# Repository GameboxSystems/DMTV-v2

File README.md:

# DMTV v2

DMTV or "Dot Matrix Television" is an embedded solution to pair with a an original GameBoy console to provide 800x600 60Hz VGA out graphics, NES controller input, custom color palettes, and toggleable scanlines.

Unlike the original DMTV, this version no longer requires an atmega32u4 for controller handling. This feature is now baked directly into the source code using a simple shift register! This allows for a simplified board and lower BOM cost than before. Also includes all new color palettes.

To access scanlines and alternate color palettes, simply press Start + Select + A/B. The toggle is executed on the falling edge of the button press.

## Changes From v1

* No atmega32u4 for controller handling. This is now done by the FPGA via the nes_controller.v
* Addition of mosfet/diode arrays to simulate button presses for the Game Boy.
* Nes Port now built in!
* Mono audio included in ribbon cable. One wire required for pro sound mod.
* Greatly reduced BOM cost
* Color palettes don't hurt the eyes as much

## Getting Started

### Prerequisites

* Assembled DMTV v2 board (keep spi flash off board until after flashing)
* Windows/Linux computer (linux HIGHLY recommended)
* [APIO Icestorm](https://apiodoc.readthedocs.io/en/stable/) (iceCube2 will **NOT** synthesize source code correctly as it is not as optimized as APIO)
	* Either compile from source using APIO Icestorm or use provided precompiled binary
	* You can find install instructions on multiple platforms [here](https://apiodoc.readthedocs.io/en/stable/source/installation.html)
* Pomona SOIC-Clip Model 5252/buspirate v3.6 combo
	* This combo is for bypassing the expensive Lattice Diamond programmer cable
	* Pomona clip: https://www.digikey.com/product-detail/en/pomona-electronics/5252/501-2059-ND/745103
	* Buspirate v3.6: https://www.sparkfun.com/products/12942
* [flashrom](https://www.flashrom.org/Flashrom) 
* Not in the BOM, but a right angle NES port is required for controller support. You can find them [here](https://www.zedlabz.com/products/zedlabz-7-pin-90-degree-female-controller-connector-port-for-nintendo-nes-console-2-pack-black)

### Flashing FPGA SPI Flash Memory

Once a binary is obtained either through synthesis of source or using the precompiled binary, connect the buspirate to the SOIC clip as shown below.

If using a binary output from APIO, you must resize the binary. Flashrom will not flash the spi memory until it is sized properly. Linux users, use the truncate command and windows users use your favorite hex editor to resize the binary.

For instructions on how to use buspirate with flashrom, use the official buspirate page on the flashrom website found here: https://flashrom.org/Bus_Pirate

After successful flash, solder to DMTV PCB.

### Notes on the HDL Code / Hardware

* Color palettes can be swapped for different color palettes if desired. The color code is RGB565 so any color space higher than that will need to be translated down. RGB888 can be added via hardware if desired as well, it will however reduce the amount of logic elements.
* If a different screen resolution is desired, swap out the current 40MHz oscillator for an oscialltor that matches timings consistant with that frequency. The code will need to be changed to reflect the profile as well. Use VGA profiles found here: http://tinyvga.com/vga-timing
* Resistor values go from greatest to smallest and are assigned such that the least significant assigned output pin for RGB goes to the highest ohm resistor downwards
	* i.e. R0 -> 8kohm, G -> 16kohm, B -> 8kohm, etc.

## Currently Known Issues

* Non currently found, please submit a pull request if you find one

## ToDo

* Add option to flash SPI flash via header instead
	* This was a challenge as there needs to be a way to sever the 3.3v power rail. If the SPI flash and the FPGA both have power then the SPI flash is not detected. The only work around known is to flash the SPI flash off the board and solder it on after flashing.
* SNES controller support

## Built With

* [APIO Icestorm](https://github.com/FPGAwars/apio)
* flashrom
* Eagle
* Sublime Text

## Versions

v1.0 - Initial release

## Contributing

Please feel free to issue a PR or edit code freely. Would love to have people contribute ideas!

## Authors

* **Postman** - *Head of engineering at Gamebox Systems*

## License

This project is licensed under the GPL-3.0 license, see attached license for info.

## Acknowledgments

* **ahhuhtal** - *DMTV v2 is based off of their gbvga project. Ahhuhtal, thank you for your wonderful description of how the first active pixel is after the falling edge of HSync. I was stuck on that for a long time.* - [ahhuhtal](https://github.com/ahhuhtal)

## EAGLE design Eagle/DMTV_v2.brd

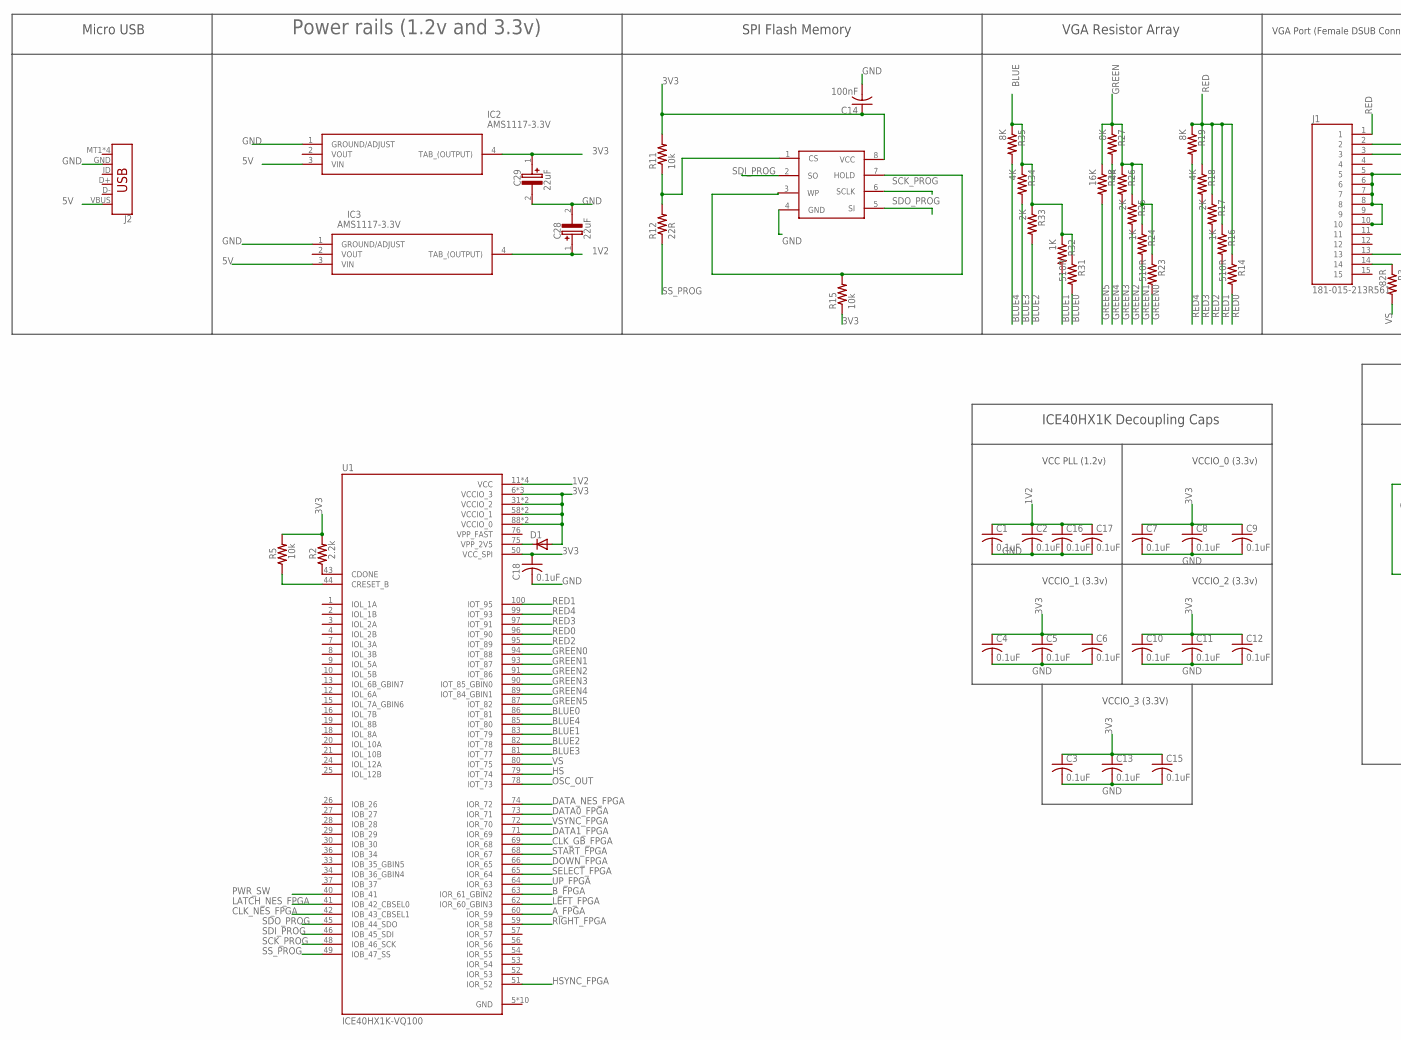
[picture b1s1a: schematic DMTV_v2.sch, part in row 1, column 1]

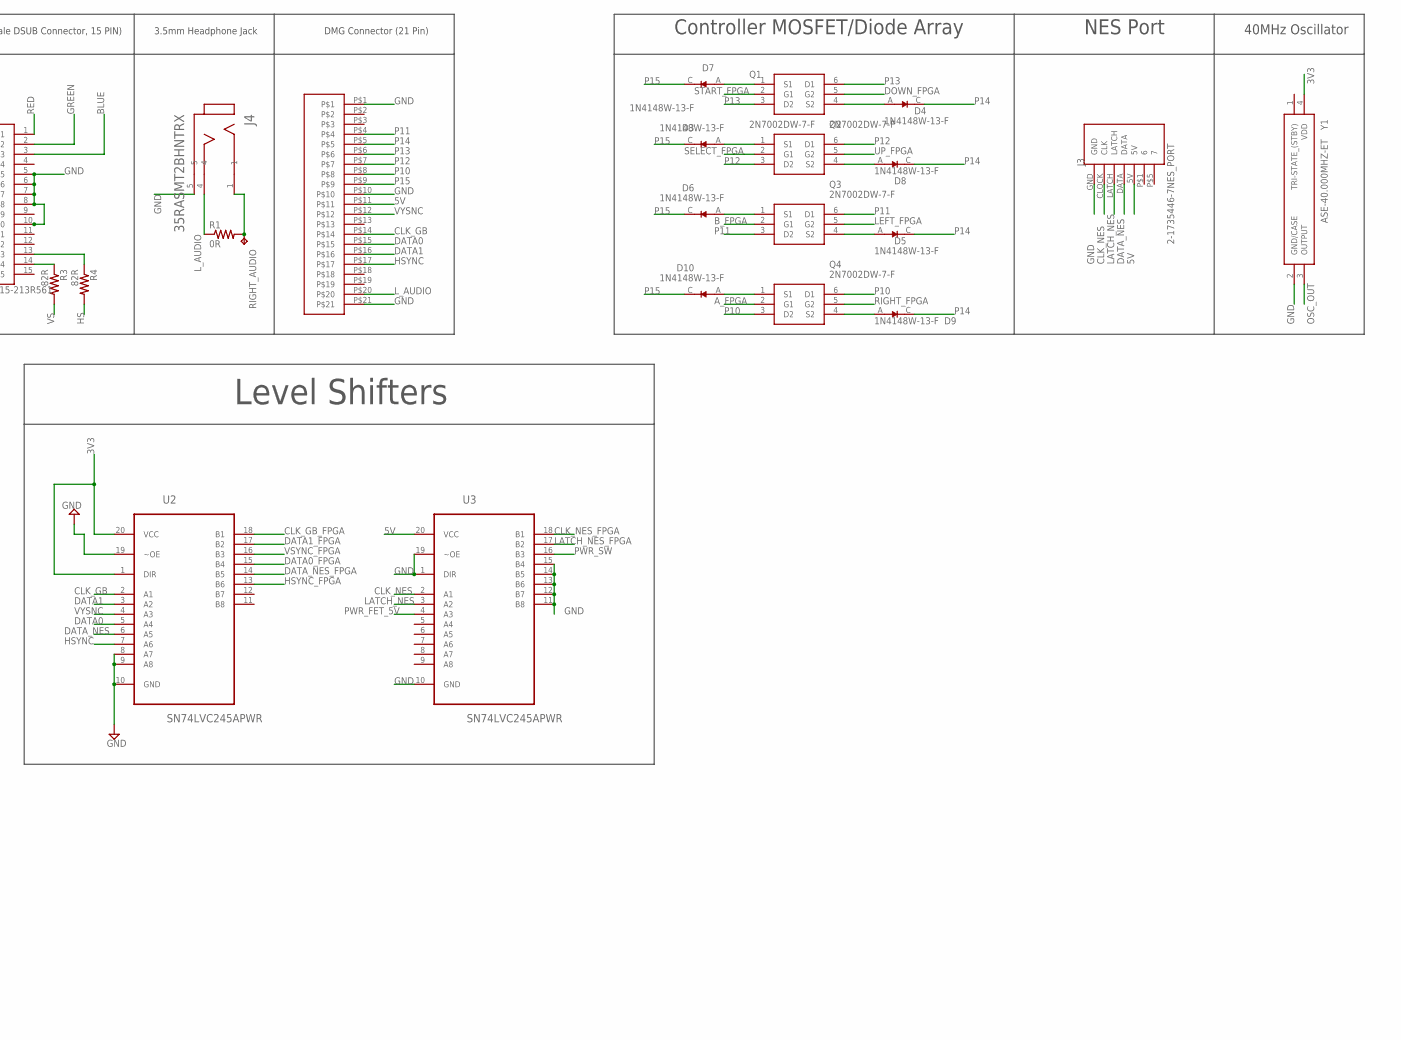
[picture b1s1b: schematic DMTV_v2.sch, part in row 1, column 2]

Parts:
C1, C2, C3, C4, C5, C6, C7, C8, C9, C10, C11, C12, C13, C15, C16, C17, C18: 0.1uF; C0603
C14: 100nF; C0603
C28, C29: 22uF; CAPPM3216X180N
D1: D-SOD123; SOD123
D3, D4, D5, D6, D7, D8, D9, D10: 1N4148W-13-F; SOD3715X135N
IC2, IC3: AMS1117-3.3V; SOT229P700X180-4N
J1: 181-015-213R561; NORCOMP_181-015-213R561
J2: USB_MICRO-B_SMT; USB-MICROB
J3: 2-1735446-7NES_PORT; NES_CONTROLLER_SOLDER_JACK
J4: 35RASMT2BHNTRX; SWITCHCRAFT_35RASMT2BHNTRX
Q1, Q2, Q3, Q4: 2N7002DW-7-F; SOT65P210X100-6N
R1: 0R; R0603
R2: 2.2k; R0603
R3, R4: 82R; R0603
R5, R11, R15: 10k; R0603
R12: 22R; R0603
R14, R23, R31: 510R; R0603
R16, R24, R32: 1K; R0603
R17, R25, R33: 2K; R0603
R18, R26, R34: 4K; R0603
R19, R27, R35: 8K; R0603
R28: 16K; R0603
RIGHT_AUDIO: TPB2,54; B2,54
U1: ICE40HX1K-VQ100; QFP50P1600X1600X120-100N
U2, U3: SN74LVC245APWR; SOP65P640X120-20N
U$5: MX25L1006EMI-10G; SOIC-8
U$6: 52808-21700520452145; 0520452145
Y1: ASE-40.000MHZ-ET; ASE40000MHZET

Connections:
1V2: C1.1, C2.1, C16.1, C17.1, C28.1 (+), IC3.4 (TAB_(OUTPUT)), U1.11 (VCC), U1.35 (VCC), U1.61 (VCC), U1.77 (VCC)
3V3: C3.1, C4.1, C5.1, C6.1, C7.1, C8.1, C9.1, C10.1, C11.1, C12.1, C13.1, C14.1, C15.1, C18.1, C29.1 (+), D1.2 (A), IC2.4 (TAB_(OUTPUT)), R2.2, R5.2, R11.2, R15.1, U1.6 (VCCIO_3), U1.14 (VCCIO_3), U1.22 (VCCIO_3), U1.31 (VCCIO_2), U1.38 (VCCIO_2), U1.50 (VCC_SPI), U1.58 (VCCIO_1), U1.67 (VCCIO_1), U1.88 (VCCIO_0), U1.92 (VCCIO_0), U2.1 (DIR), U2.20 (VCC), U$5.8 (VCC), Y1.4 (VDD)
5V: IC2.3 (VIN), IC3.3 (VIN), J2.VBUS, J3.5V, U3.20 (VCC), U$6.P$11
A_FPGA: Q4.2 (G1), U1.60 (IOR_59)
BLUE: J1.3, R31.1, R32.1, R33.1, R34.1, R35.1
BLUE0: R31.2, U1.86 (IOT_81)
BLUE1: R32.2, U1.83 (IOT_79)
BLUE2: R33.2, U1.82 (IOT_78)
BLUE3: R34.2, U1.81 (IOT_77)
BLUE4: R35.2, U1.85 (IOT_80)
B_FPGA: Q3.2 (G1), U1.63 (IOR_61_GBIN2)
CLK_GB: U2.2 (A1), U$6.P$14
CLK_GB_FPGA: U1.69 (IOR_68), U2.18 (B1)
CLK_NES: J3.CLOCK (CLK), U3.2 (A1)
CLK_NES_FPGA: U1.42 (IOB_43_CBSEL1), U3.18 (B1)
DATA0: U2.5 (A4), U$6.P$15
DATA0_FPGA: U1.73 (IOR_71), U2.15 (B4)
DATA1: U2.3 (A2), U$6.P$16
DATA1_FPGA: U1.71 (IOR_69), U2.17 (B2)
DATA_NES: J3.DATA, U2.6 (A5)
DATA_NES_FPGA: U1.74 (IOR_72), U2.14 (B5)
DOWN_FPGA: Q1.5 (G2), U1.66 (IOR_65)
GND: C1.2, C2.2, C3.2, C4.2, C5.2, C6.2, C7.2, C8.2, C9.2, C10.2, C11.2, C12.2, C13.2, C14.2, C15.2, C16.2, C17.2, C18.2, C28.2 (-), C29.2 (-), IC2.1 (GROUND/ADJUST), IC3.1 (GROUND/ADJUST), J1.5, J1.6, J1.7, J1.8, J1.10, J2.GND, J3.GND, J4.5, U1.5 (GND), U1.17 (GND), U1.23 (GND), U1.32 (GND), U1.39 (GND), U1.47 (GND), U1.55 (GND), U1.70 (GND), U1.84 (GND), U1.98 (GND), U2.8 (A7), U2.9 (A8), U2.10 (GND), U2.19 (~OE), U3.1 (DIR), U3.10 (GND), U3.11 (B8), U3.12 (B7), U3.13 (B6), U3.14 (B5), U3.15 (B4), U3.19 (~OE), U$5.4 (GND), U$6.P$1, U$6.P$10, U$6.P$21, Y1.2 (GND/CASE)
GREEN: J1.2, R23.1, R24.1, R25.1, R26.1, R27.1, R28.1
GREEN0: R23.2, U1.94 (IOT_88)
GREEN1: R24.2, U1.93 (IOT_87)
GREEN2: R25.2, U1.91 (IOT_86)
GREEN3: R26.2, U1.90 (IOT_85_GBIN0)
GREEN4: R27.2, U1.89 (IOT_84_GBIN1)
GREEN5: R28.2, U1.87 (IOT_82)
HS: R4.2, U1.79 (IOT_74)
HSYNC: U2.7 (A6), U$6.P$17
HSYNC_FPGA: U1.51 (IOR_52), U2.13 (B6)
LATCH_NES: J3.LATCH, U3.3 (A2)
LATCH_NES_FPGA: U1.41 (IOB_42_CBSEL0), U3.17 (B2)
LEFT_FPGA: Q3.5 (G2), U1.62 (IOR_60_GBIN3)
L_AUDIO: J4.4, R1.1, U$6.P$20
unnamed: D1.1 (C), U1.75 (VPP_2V5)
unnamed: D7.A, Q1.1 (S1)
unnamed: J1.14, R3.1
unnamed: J1.13, R4.1
unnamed: J4.1, R1.2, RIGHT_AUDIO.TP
unnamed: R2.1, U1.43 (CDONE)
unnamed: R5.1, U1.44 (CRESET_B)
unnamed: R11.1, R12.2, U$5.1 (CS)
unnamed: D4.A, Q1.4 (S2)
unnamed: D3.A, Q2.1 (S1)
unnamed: D8.A, Q2.4 (S2)
unnamed: R15.2, U$5.3 (WP), U$5.7 (HOLD)
unnamed: D5.A, Q3.4 (S2)
unnamed: D9.A, Q4.4 (S2)
unnamed: D10.A, Q4.1 (S1)
unnamed: D6.A, Q3.1 (S1)
OSC_OUT: U1.78 (IOT_73), Y1.3 (OUTPUT)
P10: Q4.3 (D2), Q4.6 (D1), U$6.P$8
P11: Q3.3 (D2), Q3.6 (D1), U$6.P$4
P12: Q2.3 (D2), Q2.6 (D1), U$6.P$7
P13: Q1.3 (D2), Q1.6 (D1), U$6.P$6
P14: D4.C (K), D5.C (K), D8.C (K), D9.C (K), U$6.P$5
P15: D3.C (K), D6.C (K), D7.C (K), D10.C (K), U$6.P$9
PWR_FET_5V: U3.4 (A3)
PWR_SW: U1.40 (IOB_41), U3.16 (B3)
RED: J1.1, R14.1, R16.1, R17.1, R18.1, R19.1
RED0: R14.2, U1.96 (IOT_90)
RED1: R16.2, U1.100 (IOT_95)
RED2: R17.2, U1.95 (IOT_89)
RED3: R18.2, U1.97 (IOT_91)
RED4: R19.2, U1.99 (IOT_93)
RIGHT_FPGA: Q4.5 (G2), U1.59 (IOR_58)
SCK_PROG: U1.48 (IOB_46_SCK), U$5.6 (SCLK)
SDI_PROG: U1.46 (IOB_45_SDI), U$5.2 (SO)
SDO_PROG: U1.45 (IOB_44_SDO), U$5.5 (SI)
SELECT_FPGA: Q2.2 (G1), U1.65 (IOR_64)
SS_PROG: R12.1, U1.49 (IOB_47_SS)
START_FPGA: Q1.2 (G1), U1.68 (IOR_67)
UP_FPGA: Q2.5 (G2), U1.64 (IOR_63)
VPP_FAST: U1.76 (VPP_FAST)
VS: R3.2, U1.80 (IOT_75)
VSYNC_FPGA: U1.72 (IOR_70), U2.16 (B3)
VYSNC: U2.4 (A3), U$6.P$12

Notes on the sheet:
VCC PLL (1.2v)
VCCIO_0 (3.3v)
VCCIO_1 (3.3v)
VCCIO_2 (3.3v)
VCCIO_3 (3.3V)
ICE40HX1K Decoupling Caps
VGA Resistor Array
VGA Port (Female DSUB Connector, 15 PIN)
SPI Flash Memory
Power rails (1.2v and 3.3v)
Level Shifters
3.5mm Headphone Jack
DMG Connector (21 Pin)
Micro USB
Controller MOSFET/Diode Array
NES Port
40MHz Oscillator

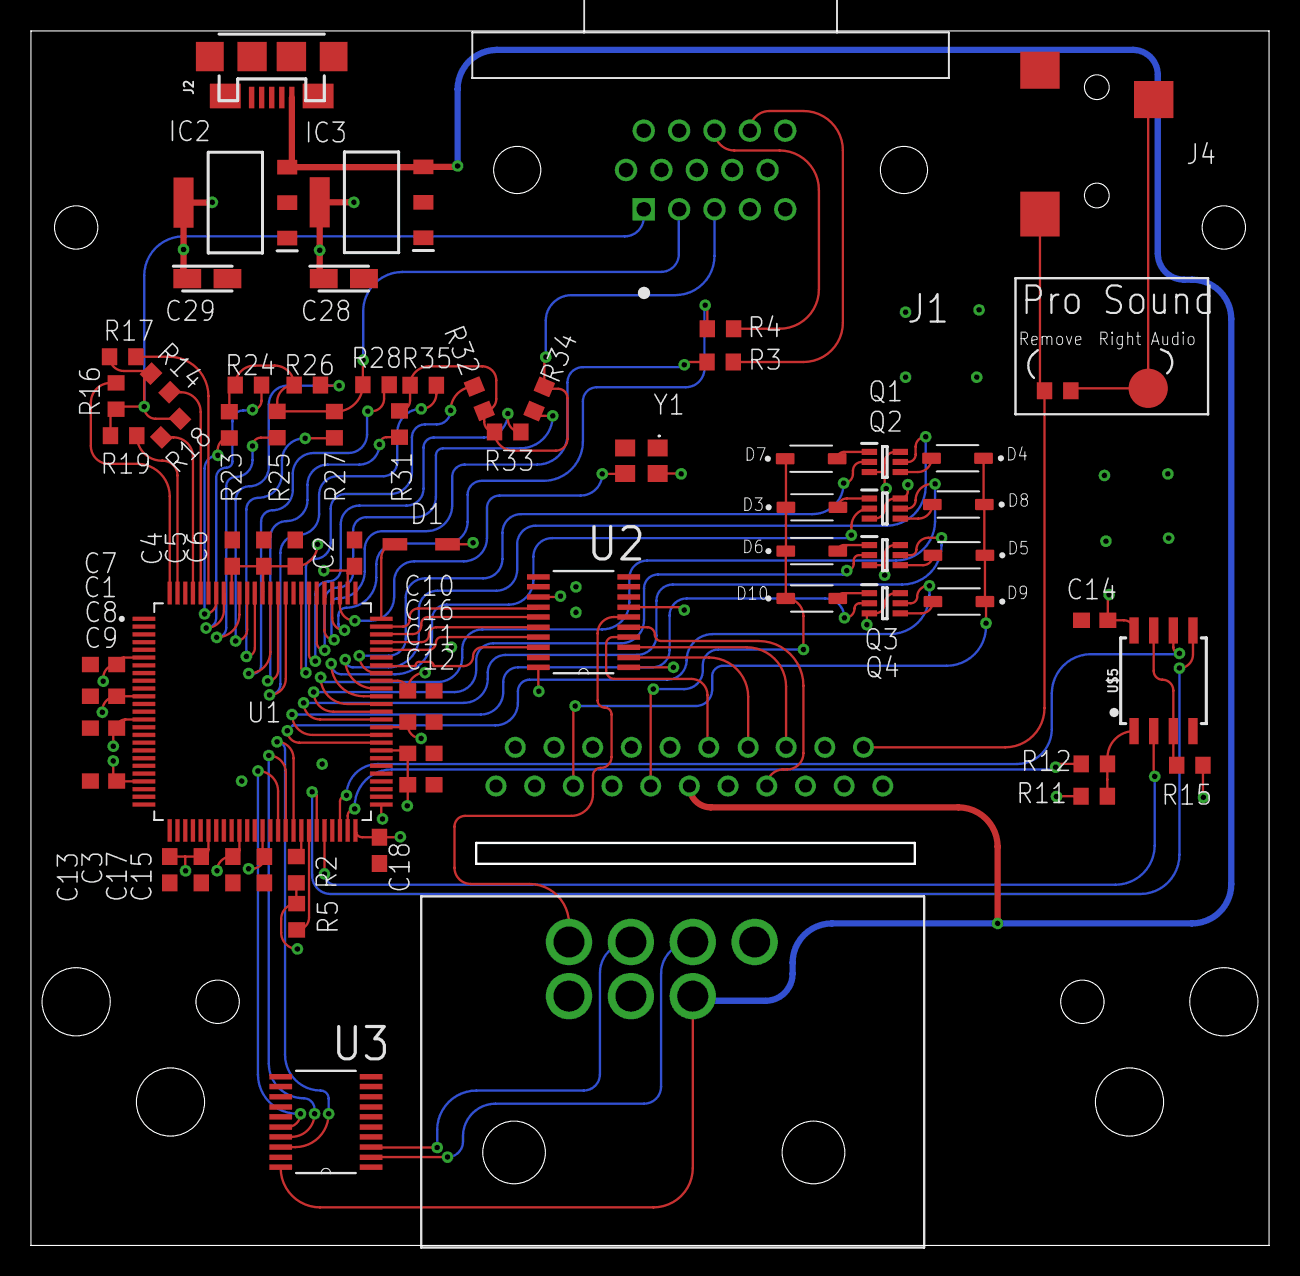
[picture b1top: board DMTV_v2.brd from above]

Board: 4 copper layers, 79.9 x 78.3 mm, 71 parts (1 on the bottom side), 78 nets.

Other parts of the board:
U$1: DMTVPLS

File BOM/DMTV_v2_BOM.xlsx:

Qty | Value | Package | Parts
17 | 0.1uF | C0603 | C1, C2, C3, C4, C5, C6, C7, C8, C9, C10, C11, C12, C13, C15, C16, C17, C18
1 | 100nF | C0603 | C14
2 | 22uF | CAPPM3216X180N | C28, C29
1 |  | SOD123 | D1
8 | 1N4148W-13-F | SOD3715X135N | D3, D4, D5, D6, D7, D8, D9, D10
1 | AMS1117-3.3 | SOT229P700X180-4N | IC2
1 | AMS1117-1.2 | SOT229P700X180-4N | IC3
1 | 181-015-213R561 | NORCOMP_181-015-213R561 | J1
1 |  | USB-MICROB | J2
1 | 2-1735446-7NES_PORT | NES_CONTROLLER_SOLDER_JACK | J3
1 | 35RASMT2BHNTRX | SWITCHCRAFT_35RASMT2BHNTRX | J4
4 | 2N7002DW-7-F | SOT65P210X100-6N | Q1, Q2, Q3, Q4
1 | 0R | R0603 | R1
1 | 22R | R0603 | R12
3 | 510R | R0603 | R14, R23, R31
3 | 1K | R0603 | R16, R24, R32
3 | 2K | R0603 | R17, R25, R33
3 | 4K | R0603 | R18, R26, R34
3 | 8K | R0603 | R19, R27, R35
1 | 2.2k | R0603 | R2
1 | 16K | R0603 | R28
2 | 82R | R0603 | R3, R4
3 | 10k | R0603 | R5, R11, R15
1 | MX25L1006EMI-10G | SOIC-8 | U$5
1 | 52808-21700520452145 | 520452145 | U$6
1 | ICE40HX1K-VQ100 | QFP50P1600X1600X120-100N | U1
2 | SN74LVC245APWR | SOP65P640X120-20N | U2, U3
1 | SI2301BDS | SOT95P240X111-3N | U5
1 | ASE-40.000MHZ-ET | SMD-3225_4P | Y1

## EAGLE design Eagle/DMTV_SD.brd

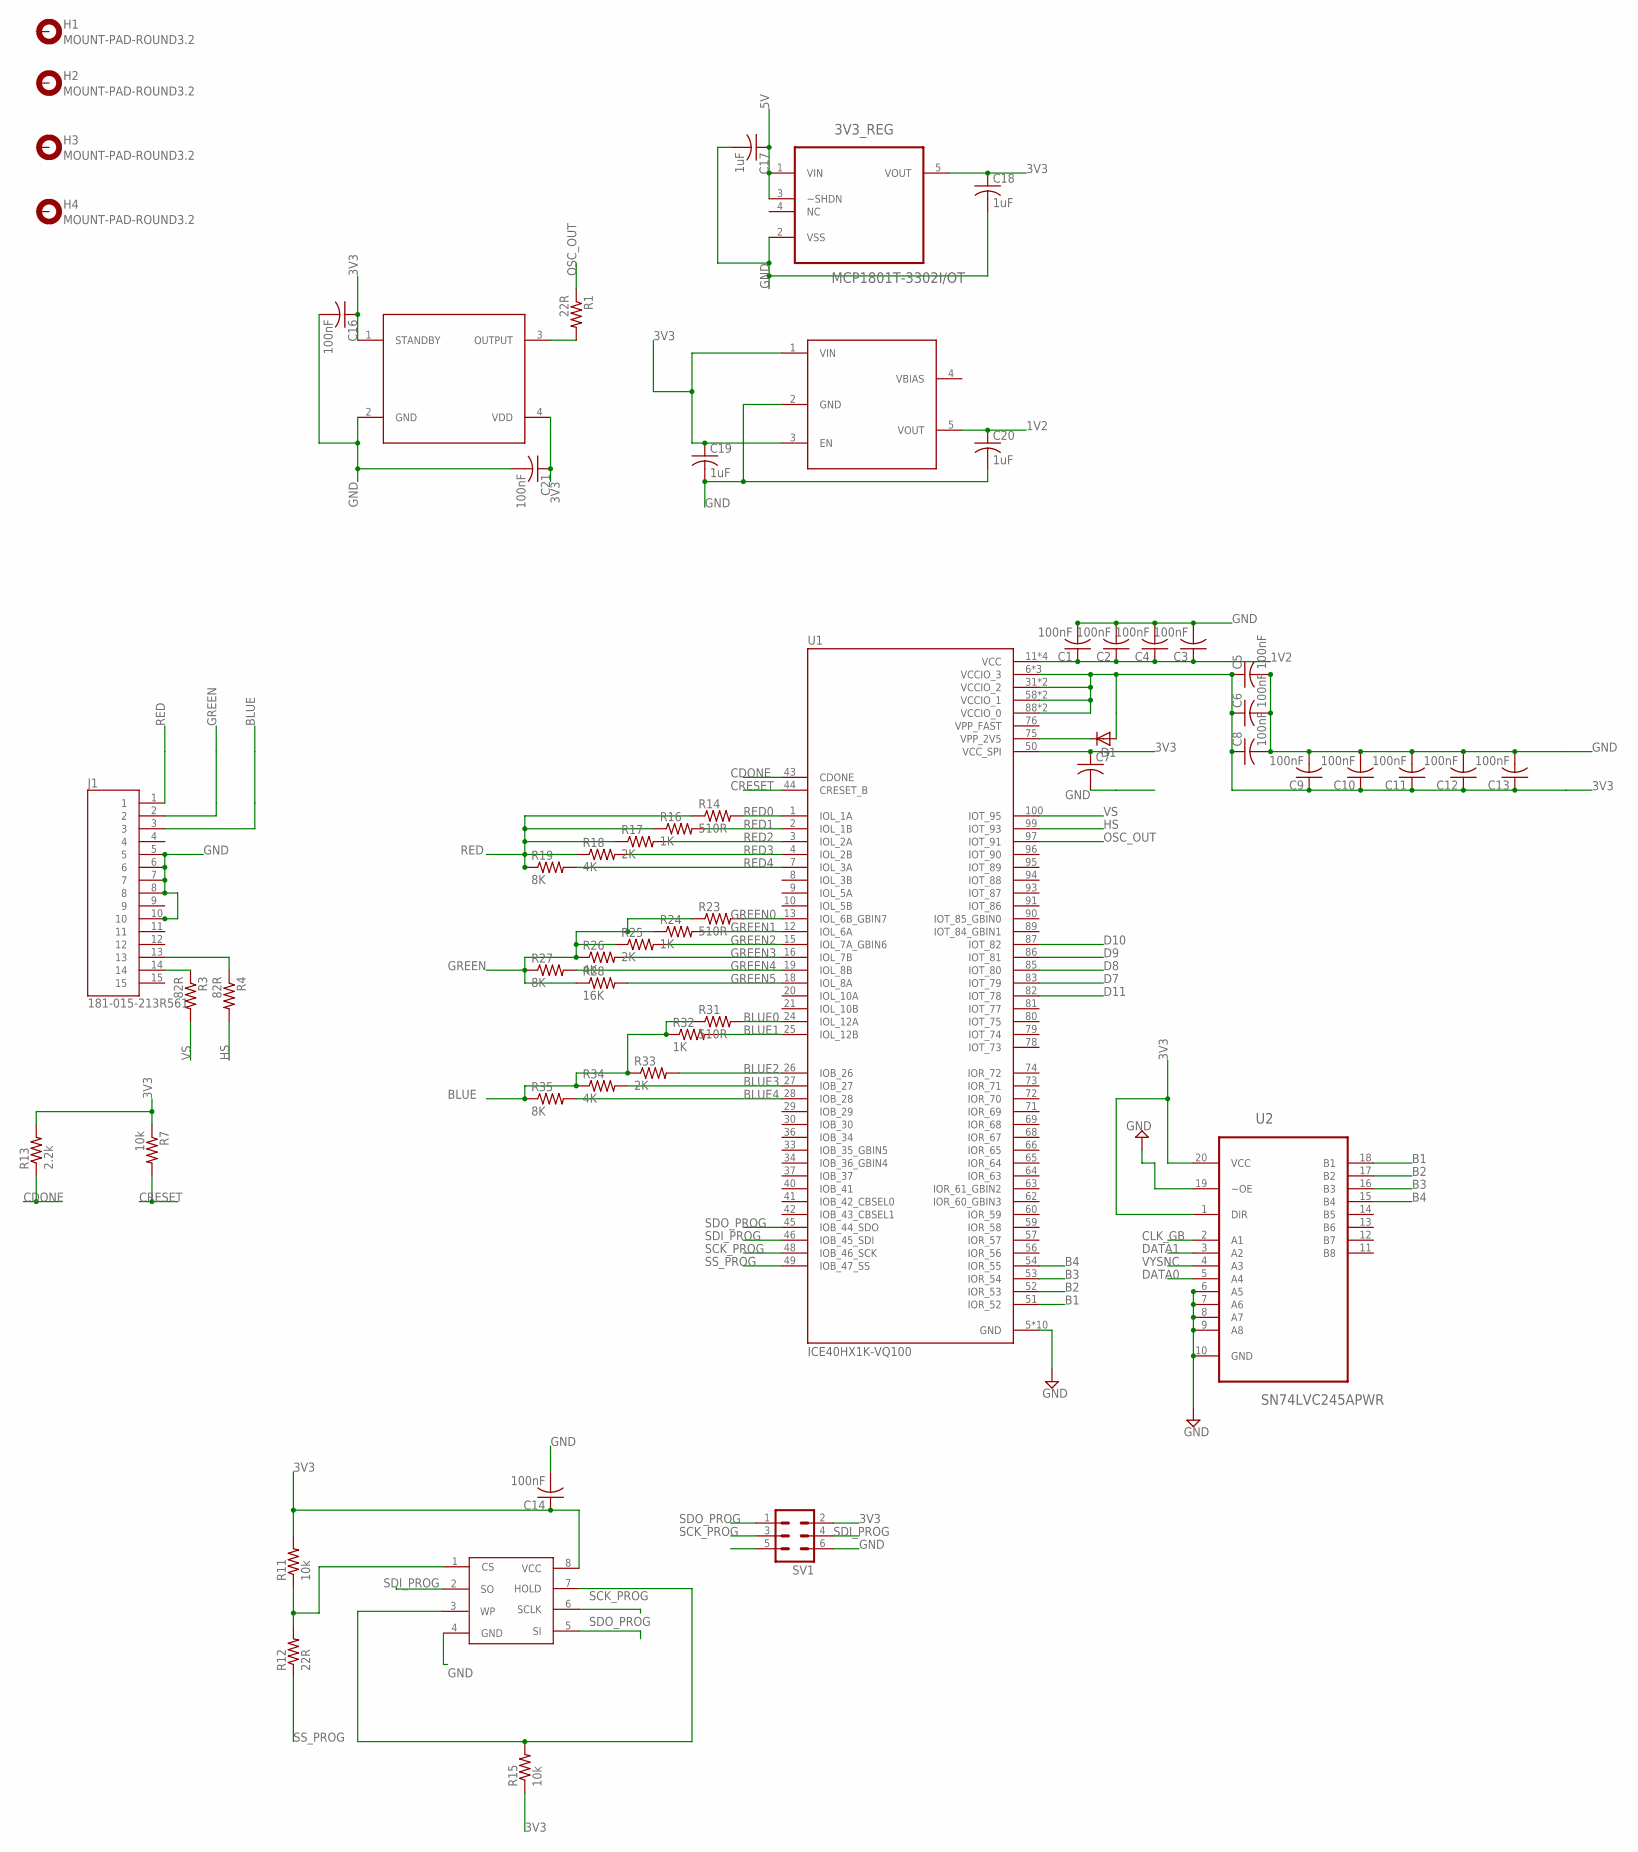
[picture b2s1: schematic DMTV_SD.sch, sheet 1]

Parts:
3V3_REG: MCP1801T-3302I/OT; SOT95P270X145-5N
C1, C2, C3, C4, C5, C6, C8, C9, C10, C11, C12, C13, C14, C16, C21: 100nF; C0603
C7: C-USC0603; C0603
C17, C18, C19, C20: 1uF; C0805
D1: D-SOD123; SOD123
H1, H2, H3, H4: MOUNT-PAD-ROUND3.2; 3,2-PAD
J1: 181-015-213R561; NORCOMP_181-015-213R561
R1, R12: 22R; R0603
R3, R4: 82R; R0603
R7, R11, R15: 10k; R0603
R13: 2.2k; R0603
R14, R23, R31: 510R; R0603
R16, R24, R32: 1K; R0603
R17, R25, R33: 2K; R0603
R18, R26, R34: 4K; R0603
R19, R27, R35: 8K; R0603
R28: 16K; R0603
SV1: MA03-2
U1: ICE40HX1K-VQ100; QFP50P1600X1600X120-100N
U2: SN74LVC245APWR; SOP65P640X120-20N
U$1: SIT8008BI-13-18E-25.175000G; XTAL_ASDM1-25.000MHZ-LC-T
U$2: TLV70012DDCR; SOT95P280X100-5N
U$5: MX25L1006EMI-10G; SOIC-8

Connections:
1V2: C1.1, C2.1, C3.1, C4.1, C20.1, U1.11 (VCC), U1.35 (VCC), U1.61 (VCC), U1.77 (VCC), U$2.5 (VOUT)
3V3: 3V3_REG.5 (VOUT), C5.1, C6.1, C7.1, C8.1, C9.1, C10.1, C11.1, C12.1, C13.1, C14.1, C16.1, C18.1, C19.1, C21.1, D1.2 (A), R7.1, R11.2, R13.2, R15.1, SV1.2, U1.6 (VCCIO_3), U1.14 (VCCIO_3), U1.22 (VCCIO_3), U1.31 (VCCIO_2), U1.38 (VCCIO_2), U1.50 (VCC_SPI), U1.58 (VCCIO_1), U1.67 (VCCIO_1), U1.88 (VCCIO_0), U1.92 (VCCIO_0), U2.1 (DIR), U2.20 (VCC), U$1.1 (STANDBY), U$1.4 (VDD), U$2.1 (VIN), U$2.3 (EN), U$5.8 (VCC)
5V: 3V3_REG.1 (VIN), 3V3_REG.3 (~SHDN), C17.1; also elsewhere on the board
B1: U1.51 (IOR_52), U2.18 (B1)
B2: U1.52 (IOR_53), U2.17 (B2)
B3: U1.53 (IOR_54), U2.16 (B3)
B4: U1.54 (IOR_55), U2.15 (B4)
BLUE: J1.3, R31.1, R32.1, R33.1, R34.1, R35.1
BLUE0: R31.2, U1.24 (IOL_12A)
BLUE1: R32.2, U1.25 (IOL_12B)
BLUE2: R33.2, U1.26 (IOB_26)
BLUE3: R34.2, U1.27 (IOB_27)
BLUE4: R35.2, U1.28 (IOB_28)
CDONE: R13.1, U1.43 (CDONE)
CLK_GB: U2.2 (A1); also elsewhere on the board
CRESET: R7.2, U1.44 (CRESET_B)
D7: U1.83 (IOT_79); also elsewhere on the board
D8: U1.85 (IOT_80); also elsewhere on the board
D9: U1.86 (IOT_81); also elsewhere on the board
D10: U1.87 (IOT_82); also elsewhere on the board
D11: U1.82 (IOT_78); also elsewhere on the board
DATA0: U2.5 (A4); also elsewhere on the board
DATA1: U2.3 (A2); also elsewhere on the board
GND: 3V3_REG.2 (VSS), C1.2, C2.2, C3.2, C4.2, C5.2, C6.2, C7.2, C8.2, C9.2, C10.2, C11.2, C12.2, C13.2, C14.2, C16.2, C17.2, C18.2, C19.2, C20.2, C21.2, J1.5, J1.6, J1.7, J1.8, J1.10, SV1.6, U1.5 (GND), U1.17 (GND), U1.23 (GND), U1.32 (GND), U1.39 (GND), U1.47 (GND), U1.55 (GND), U1.70 (GND), U1.84 (GND), U1.98 (GND), U2.6 (A5), U2.7 (A6), U2.8 (A7), U2.9 (A8), U2.10 (GND), U2.19 (~OE), U$1.2 (GND), U$2.2 (GND), U$5.4 (GND); also elsewhere on the board
GREEN: J1.2, R23.1, R24.1, R25.1, R26.1, R27.1, R28.1
GREEN0: R23.2, U1.13 (IOL_6B_GBIN7)
GREEN1: R24.2, U1.12 (IOL_6A)
GREEN2: R25.2, U1.15 (IOL_7A_GBIN6)
GREEN3: R26.2, U1.16 (IOL_7B)
GREEN4: R27.2, U1.19 (IOL_8B)
GREEN5: R28.2, U1.18 (IOL_8A)
HS: R4.2, U1.99 (IOT_93)
unnamed: R1.2, U$1.3 (OUTPUT)
unnamed: J1.14, R3.1
unnamed: D1.1 (C), U1.75 (VPP_2V5)
unnamed: R11.1, R12.2, U$5.1 (CS)
unnamed: J1.13, R4.1
unnamed: R15.2, U$5.3 (WP), U$5.7 (HOLD)
OSC_OUT: R1.1, U1.97 (IOT_91)
RED: J1.1, R14.1, R16.1, R17.1, R18.1, R19.1
RED0: R14.2, U1.1 (IOL_1A)
RED1: R16.2, U1.2 (IOL_1B)
RED2: R17.2, U1.3 (IOL_2A)
RED3: R18.2, U1.4 (IOL_2B)
RED4: R19.2, U1.7 (IOL_3A)
SCK_PROG: SV1.3, U1.48 (IOB_46_SCK), U$5.6 (SCLK)
SDI_PROG: SV1.4, U1.46 (IOB_45_SDI), U$5.2 (SO)
SDO_PROG: SV1.1, U1.45 (IOB_44_SDO), U$5.5 (SI)
SS_PROG: R12.1, U1.49 (IOB_47_SS)
VPP_FAST: U1.76 (VPP_FAST)
VS: R3.2, U1.100 (IOT_95)
VYSNC: U2.4 (A3); also elsewhere on the board

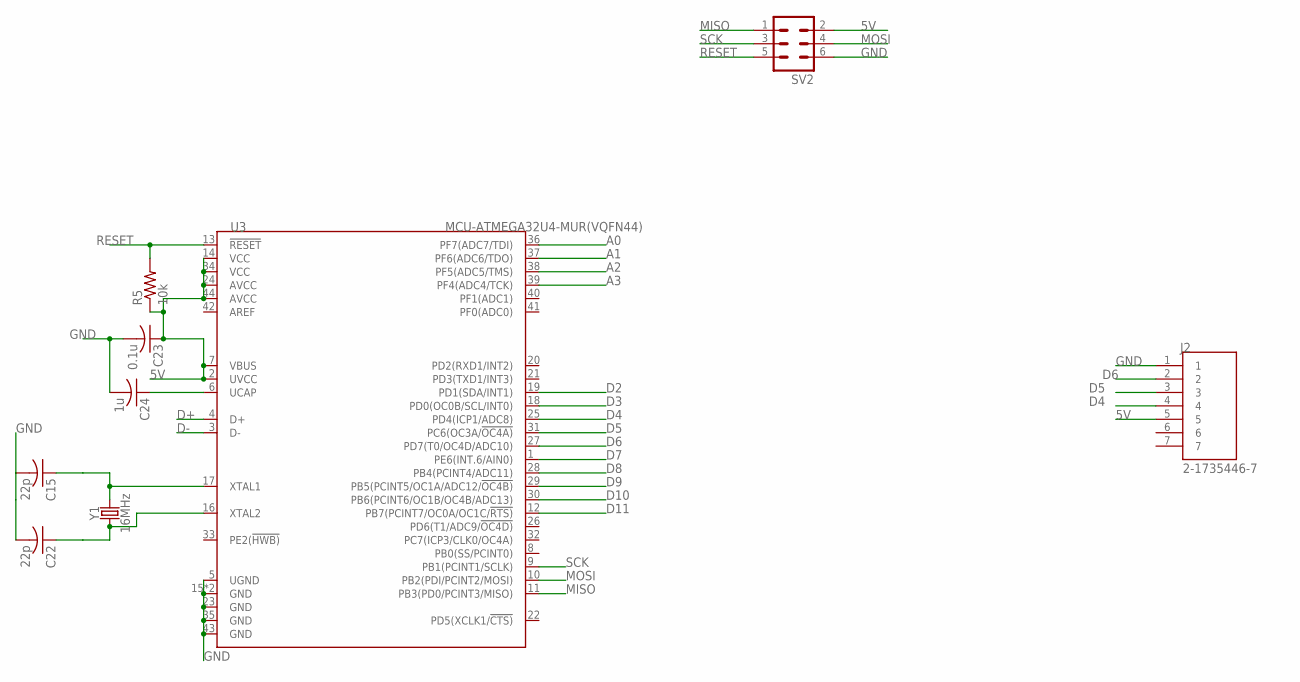
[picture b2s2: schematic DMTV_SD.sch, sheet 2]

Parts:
C15, C22: 22p; C0805
C23: 0.1u; C0805
C24: 1u; C0805
J2: 2-1735446-7; TE_2-1735446-7
R5: 10k; R0805
SV2: MA03-2
U3: MCU-ATMEGA32U4-MUR(VQFN44); QFN44G-0.5-7X7MM
Y1: 16MHz; CRYSTAL-SMD-5X3.2-4PAD

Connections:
5V: C23.1, J2.5, R5.1, SV2.2, U3.2 (UVCC), U3.7 (VBUS), U3.14 (VCC), U3.24 (AVCC), U3.34 (VCC), U3.44 (AVCC); also elsewhere on the board
A0: U3.36 (PF7(ADC7/TDI)); also elsewhere on the board
A1: U3.37 (PF6(ADC6/TDO)); also elsewhere on the board
A2: U3.38 (PF5(ADC5/TMS)); also elsewhere on the board
A3: U3.39 (PF4(ADC4/TCK)); also elsewhere on the board
D2: U3.19 (PD1(SDA/INT1)); also elsewhere on the board
D3: U3.18 (PD0(OC0B/SCL/INT0)); also elsewhere on the board
D4: J2.4, U3.25 (PD4(ICP1/ADC8))
D5: J2.3, U3.31 (PC6(OC3A/!OC4A))
D6: J2.2, U3.27 (PD7(T0/OC4D/ADC10))
D7: U3.1 (PE6(INT.6/AIN0)); also elsewhere on the board
D8: U3.28 (PB4(PCINT4/ADC11)); also elsewhere on the board
D9: U3.29 (PB5(PCINT5/OC1A/ADC12/!OC4B)); also elsewhere on the board
D10: U3.30 (PB6(PCINT6/OC1B/OC4B/ADC13)); also elsewhere on the board
D11: U3.12 (PB7(PCINT7/OC0A/OC1C/!RTS)); also elsewhere on the board
D+: U3.4 (D+)
D-: U3.3 (D-)
GND: C15.2, C22.2, C23.2, C24.2, J2.1, SV2.6, U3.5 (UGND), U3.15 (GND), U3.23 (GND), U3.35 (GND), U3.43 (GND), U3.TAB (GND); also elsewhere on the board
MISO: SV2.1, U3.11 (PB3(PD0/PCINT3/MISO))
MOSI: SV2.4, U3.10 (PB2(PDI/PCINT2/MOSI))
unnamed: C15.1, U3.17 (XTAL1), Y1.3 (2)
unnamed: C22.1, U3.16 (XTAL2), Y1.1
unnamed: C24.1, U3.6 (UCAP)
RESET: R5.2, SV2.5, U3.13 (!RESET)
SCK: SV2.3, U3.9 (PB1(PCINT1/SCLK))

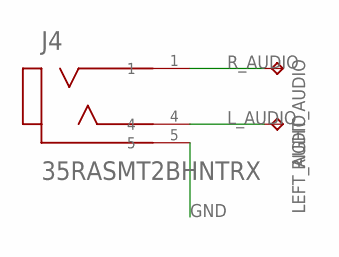
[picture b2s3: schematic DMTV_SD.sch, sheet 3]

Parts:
J4: 35RASMT2BHNTRX; SWITCHCRAFT_35RASMT2BHNTRX
LEFT_AUDIO: TPB2,54; B2,54
RIGHT_AUDIO: TPB2,54; B2,54

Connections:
GND: J4.5; also elsewhere on the board
L_AUDIO: J4.4, LEFT_AUDIO.TP
R_AUDIO: J4.1, RIGHT_AUDIO.TP

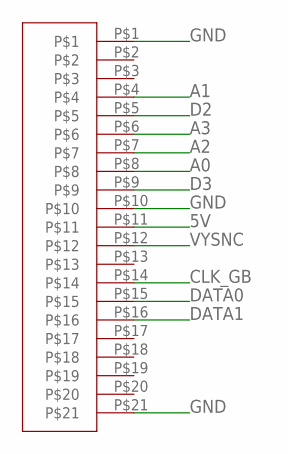
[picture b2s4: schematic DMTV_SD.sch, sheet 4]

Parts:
U$6: 52808-21700520452145; 0520452145

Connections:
5V: U$6.P$11; also elsewhere on the board
A0: U$6.P$8; also elsewhere on the board
A1: U$6.P$4; also elsewhere on the board
A2: U$6.P$7; also elsewhere on the board
A3: U$6.P$6; also elsewhere on the board
CLK_GB: U$6.P$14; also elsewhere on the board
D2: U$6.P$5; also elsewhere on the board
D3: U$6.P$9; also elsewhere on the board
DATA0: U$6.P$15; also elsewhere on the board
DATA1: U$6.P$16; also elsewhere on the board
GND: U$6.P$1, U$6.P$10, U$6.P$21; also elsewhere on the board
VYSNC: U$6.P$12; also elsewhere on the board

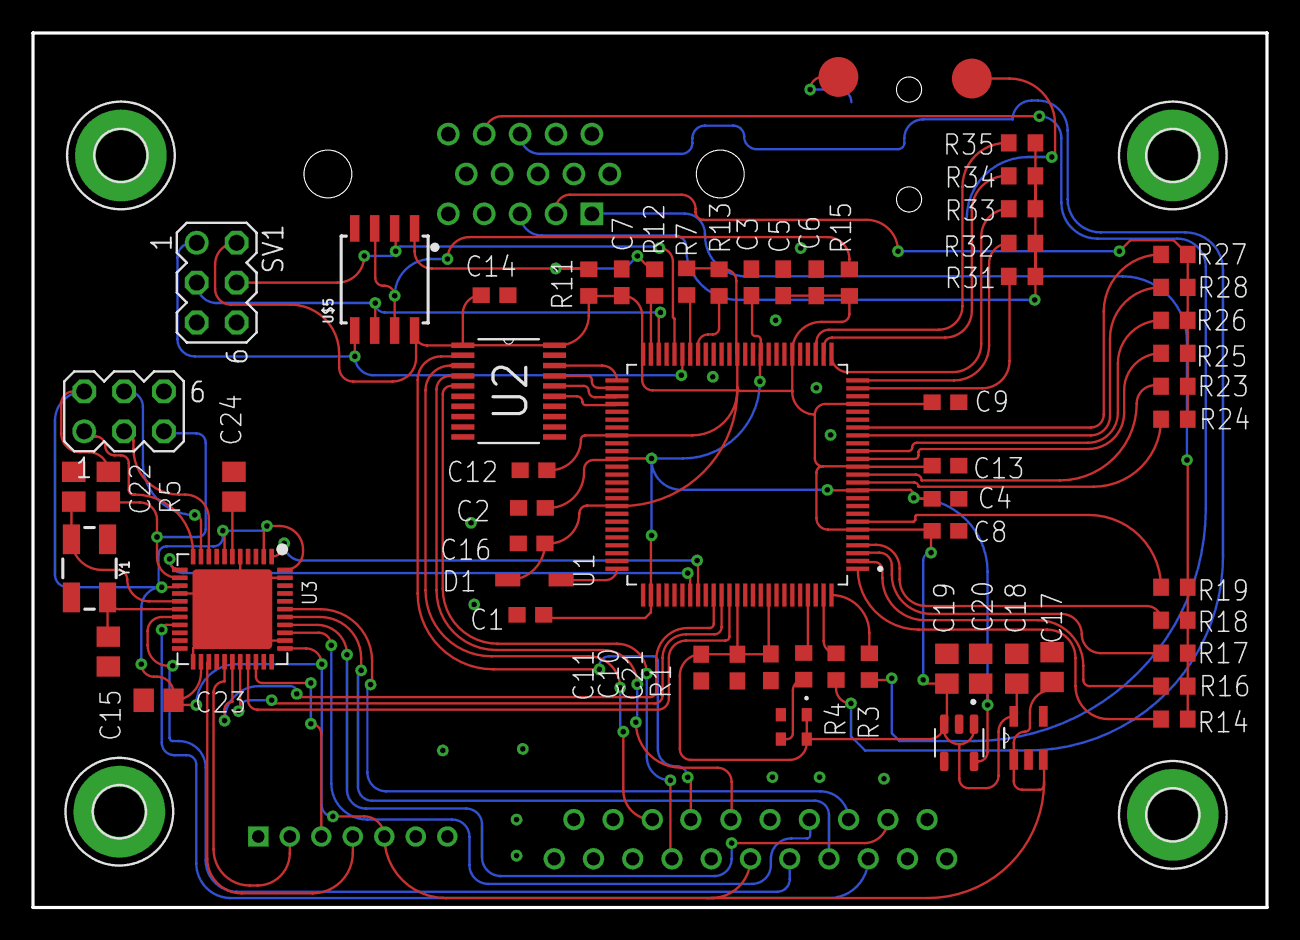
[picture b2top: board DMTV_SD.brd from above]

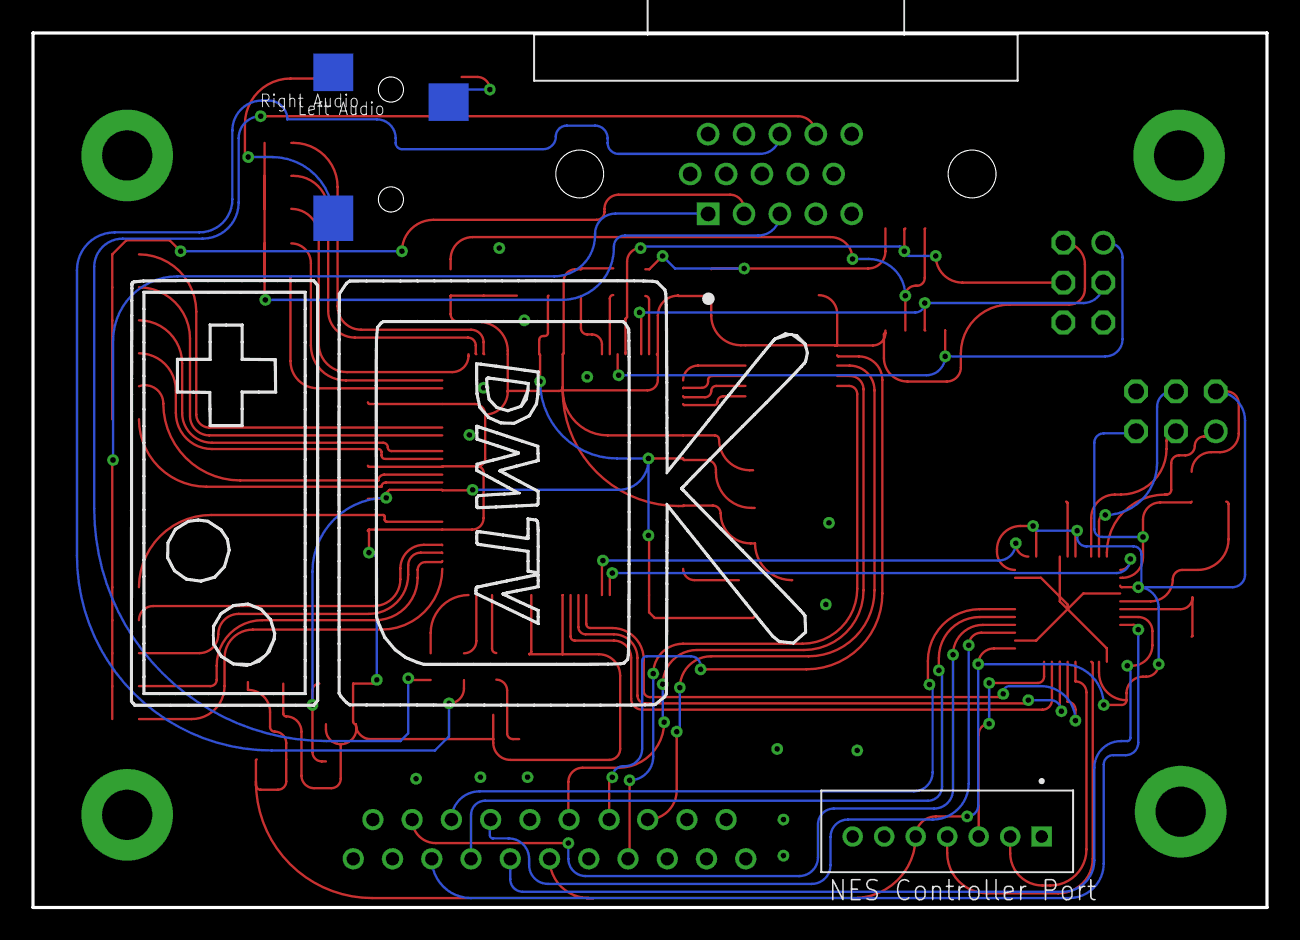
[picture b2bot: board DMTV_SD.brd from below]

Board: 2 copper layers, 78.6 x 55.7 mm, 71 parts (5 on the bottom side), 69 nets.

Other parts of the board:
U$4: DMTVPLS

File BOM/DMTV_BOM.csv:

Qty,Value,Part Num,Package,Parts,,Can Use Generic?
1,MCP1801T-3302I/OT,MCP1801T-3302I/OT,SOT-23-5,3V3_REG,,yes
15,100nF,*,C0603,"C1, C2, C3, C4, C5, C6, C8, C9, C10, C11, C12, C13, C14, C16, C21,C7",,yes
2,22p,*,C0805,"C15, C22",,yes
5,1uF,*,C0805,"C17, C18, C19, C20,C24",,yes
1,0.1u,*,C0805,C23,,yes
1,,*,SOD123,D1,,yes
1,L77HDE15SD1CH4RHNVGA,L77HDE15SD1CH4RHNVGA,,J1,,yes
1,1735446-7,1735446-7,1735446-7,J2,,yes
1,35RASMT2BHNTRX,35RASMT2BHNTRX,SWITCHCRAFT_35RASMT2BHNTRX,J4,,yes
2,22R,*,R0603,"R1, R12",,yes
1,2.2k,*,R0603,R13,,yes
3,510R,*,R0603,"R14, R23, R31",,yes
3,1K,*,R0603,"R16, R24, R32",,yes
3,2K,*,R0603,"R17, R25, R33",,yes
3,4K,*,R0603,"R18, R26, R34",,yes
3,8K,*,R0603,"R19, R27, R35",,yes
1,16K,*,R0603,R28,,yes
2,82R,*,R0603,"R3, R4",,yes
1,10k,*,R0805,R5,,yes
3,10k,*,R0603,"R7, R11, R15",,yes
1, 40MHZ,,SMD-2520_4P,U$1,,yes
1, TLV70012DDCR , TLV70012DDCR ,SOT-23-5,U$2,,yes
1,MX25L1006EMI-10G,MX25L1006EMI-10G,SOIC-8,U$5,,no
1,52808-21700520452145,520452145,520452145,U$6,,yes
1,ICE40HX1K-VQ100,ICE40HX1K-VQ100,QFP50P1600X1600X120-100N,U1,,no
1,SN74LVC245APWR,SN74LVC245APWR,SOP65P640X120-20N,U2,,no
1,MCU-ATMEGA32U4-MUR(VQFN44),ATMEGA32U4,QFN44,U3,,no
1,16MHZ,*,SMD-5X3.2-4PAD,Y1,,yes

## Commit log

2020-12-19 First Commit of DMTV v2
2020-12-19 removed arduino code
2020-12-19 Removed old verilog files and PCB layout and schematic files
2020-12-19 Removed v1 BOM
2020-12-19 Removed v1 binary
2020-12-19 Update to README - Added new link to NES port
2021-11-15 Update for correct color palettes

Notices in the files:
parts and their libraries:
SparkFun-Clocks: Licensing: Creative Commons ShareAlike 4.0 International - https://creativecommons.org/licenses/by-sa/4.0
